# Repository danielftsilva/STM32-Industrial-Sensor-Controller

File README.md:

# STM32-RF-USB-Gateway

## Overview

<p align="center">
  <a href="PDFs/STM32-RF-USB-Gateway.pdf">
    View the complete schematic PDF
  </a>
</p>

The **STM32-RF-USB-Gateway** is an embedded hardware platform developed to provide a USB interface between a computer and a **2.4 GHz nRF24L01P wireless transceiver**.

The objective of the project is to develop a compact USB-connected wireless gateway based on the **STM32L432KBU6**, allowing the microcontroller to interface with a host computer through USB while controlling the nRF24L01P through SPI.

The design incorporates dedicated power regulation, USB ESD protection, a 16 MHz crystal oscillator, an RF impedance-matching network, a 50 Ω controlled-impedance antenna path, an external SMA connector, and an SWD programming/debugging interface.

## Main Components

- **STMicroelectronics STM32L432KBU6** — main microcontroller with USB Full-Speed and SPI interfaces
- **Nordic Semiconductor nRF24L01P** — 2.4 GHz wireless transceiver
- **Torex XC6206P332MR-G** — 3.3 V LDO regulator
- **STMicroelectronics USBLC6-2SC6** — USB ESD protection
- **Samtec SMA-J-P-H-ST-EM3** — 50 Ω SMA antenna connector
- **FTSH-105-01-F-D** — SWD programming/debugging connector
- **16 MHz crystal** — nRF24L01P reference clock

### STM32 Peripheral Assignment

The STM32L432KBU6 was configured as the central controller of the gateway, with its peripherals and GPIOs assigned to the USB, nRF24L01P, SWD, and status interfaces.

<p align="center">
  <em>STM32L432KBU6 pin assignment used in the design</em>
</p>

## PCB Design

The PCB layout was developed from the finalized schematic, with dedicated areas for the USB interface, power regulation, STM32, nRF24L01P, RF matching network, SMA antenna interface, and SWD connector.

<p align="center">
  <em>Layout close-up of the STM32L432KBU6.</em>
</p>

The RF section was designed as a dedicated 50Ω controlled-impedance interface between the nRF24L01P matching network and the external SMA connector.

<p align="center">
  <em>2.4 GHz RF matching network, controlled-impedance transmission line and SMA interface</em>
</p>

## Project Status

**Work in Progress**

- Project started: **2022**
- Objective: Exploration of the **STM32L432KBU6** and its capabilities
- Schematic: **Existing gateway architecture finalized**
- PCB layout: **In progress**
- Firmware: **Started, but not completed**
- Prototype: **Not yet completed**

The current repository documents the developed USB-to-2.4 GHz RF gateway hardware. The PCB layout is being expanded before finalization to incorporate additional functionality.

## Planned Expansion

The next revision is planned to include:

- **OLED display** for local system and RF status
- **User reset button**
- **I²C environmental sensor** for temperature, humidity, pressure, etc.
- **Additional test points** for hardware debugging and validation

These additions are the reason the current PCB layout remains unfinished. The existing gateway schematic is finalized, while the new features still need to be incorporated into the schematic and PCB before the hardware can be considered complete.

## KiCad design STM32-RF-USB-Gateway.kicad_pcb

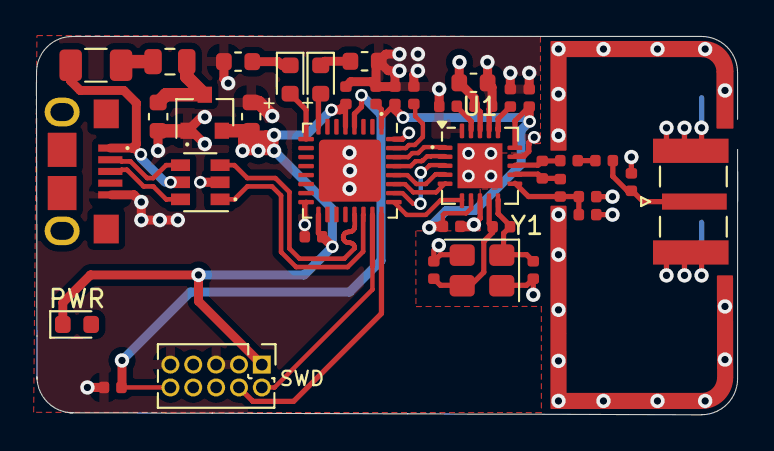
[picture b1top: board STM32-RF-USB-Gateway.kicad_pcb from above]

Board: 4 copper layers, 39.0 x 21.0 mm, 39 parts (0 on the bottom side), 26 nets.

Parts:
C1, C2, C8: 10u; C_0603_1608Metric
C3, C5, C6, C7: 100n; C_0402_1005Metric
C4: 1u; C_0402_1005Metric
C9, C10, C11: 10n; C_0402_1005Metric
C12: 33n; C_0402_1005Metric
C13, C14: 12p; C_0402_1005Metric
C15: 1p5; C_0402_1005Metric
C16: 1p; C_0402_1005Metric
C17: 2n2; C_0402_1005Metric
C18: 4p7; C_0402_1005Metric
D1: GR; LED_0603_1608Metric
D2: YE; LED_0603_1608Metric
F1: 100mA; Fuse_1206_3216Metric
FB1: 100 @ 100MHz; L_0805_2012Metric
J1: USB_B_Micro; 101181930001LF
J2: SMA; SMA_Samtec_SMA-J-P-X-ST-EM1_EdgeMount
J3: ARM 10pin; PinHeader_2x05_P1.27mm_Vertical
L1: 3n9; L_0402_1005Metric
L2: 8n2; L_0402_1005Metric
L3: 2n7; L_0402_1005Metric
PWR: APT1608SURC; LED_0603_1608Metric
R1: 2k2; R_0402_1005Metric
R2, R3: 2k2; R_0603_1608Metric
R4: 22k; R_0402_1005Metric
R5: 1M; R_0402_1005Metric
U1: XC6206P332MR; SOT-23
U1#2: nRF24L01P; QFN-20-1EP_4x4mm_P0.5mm_EP2.5x2.5mm
U2: USBLC6-2SC6; SOT-23-6
U3: STM32L432KBU6; QFN-32-1EP_5x5mm_P0.5mm_EP3.45x3.45mm
Y1: 16MHz; Crystal_SMD_3225-4Pin_3.2x2.5mm

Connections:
3V3: C2.1, C4.1, C5.1, C6.1, C7.1, C9.1, C10.1, J3.1, PWR.1 (A), U1.2, U1#2.7 (VDD), U1#2.15 (VDD), U1#2.18 (VDD), U3.1, U3.5, U3.17
+3V3: C8.1, C11.1
+5V: F1.2, J1.1, U2.5
/NRF_XC1: U1#2.10 (XC1), Y1.1
/NRF_XC2: U1#2.9 (XC2), Y1.3
GND: C1.2, C2.2, C3.2, C4.2, C5.2, C6.2, C7.2, C8.2, C9.2, C10.2, C11.2, C12.2, C13.2, C14.2, C16.1, C17.1, C18.1, J1.5, J2.2, J3.3, J3.5, J3.9, R1.2, R2.2, R3.2, R4.2, U1.1, U1#2.8 (VSS), U1#2.14 (VSS), U1#2.17 (VSS), U1#2.20 (VSS), U2.2, U3.16, U3.32, U3.33, Y1.2, Y1.4
NRF_ANT1: L2.2, L3.2
NRF_ANT2: L1.1, L2.1
NRF_VDD_PA: C17.2, C18.2, L3.1
NRF_XC1: C13.1, R5.2
NRF_XC2: C14.1, R5.1
NRST: C3.1, J3.10, U3.4
unnamed: C1.1, U1.3
unnamed: C15.1, C16.2, J2.1
unnamed: C15.2, L1.2
unnamed: D1.1, R2.1
unnamed: D1.2, U3.9
unnamed: D2.1, R3.1
unnamed: D2.2, U3.8
unnamed: R1.1, U3.31
SWCLK: J3.4, U3.24
SWDIO: J3.2, U3.23
USB_CONN_D+: J1.3, U2.6
USB_CONN_D-: J1.2, U2.4
USB_D+: U2.1, U3.22
USB_D-: U2.3, U3.21
